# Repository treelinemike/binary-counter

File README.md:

# binary-counter
AVR binary counter for LED display - used to check synchronization of stereo camera systems

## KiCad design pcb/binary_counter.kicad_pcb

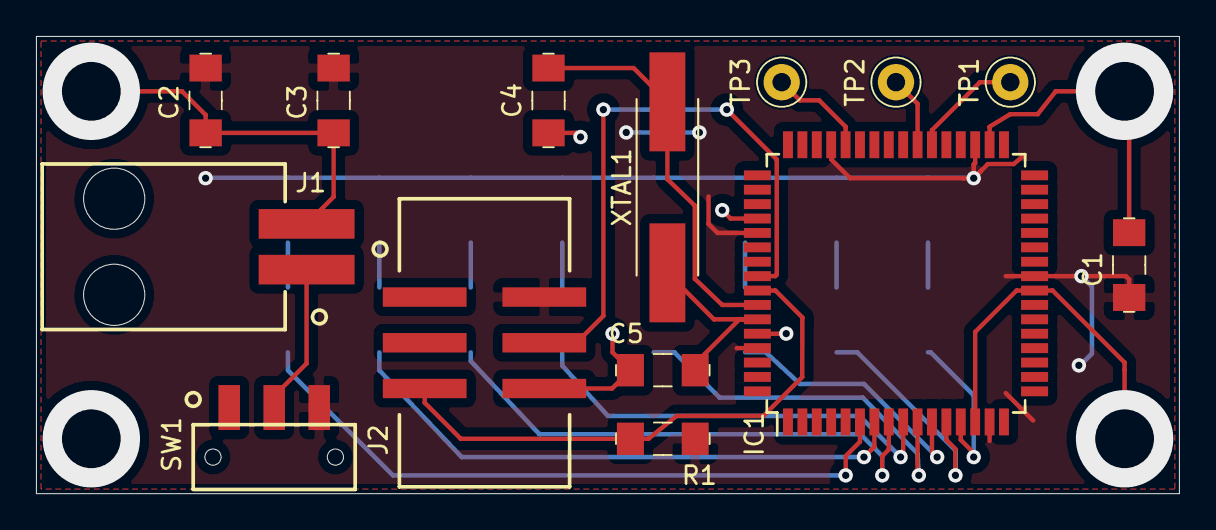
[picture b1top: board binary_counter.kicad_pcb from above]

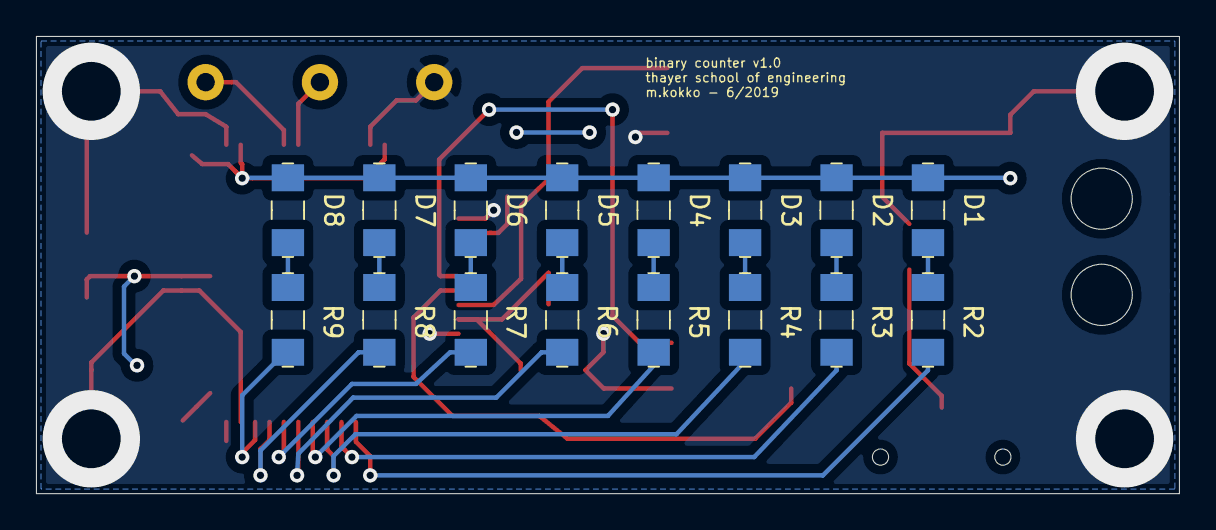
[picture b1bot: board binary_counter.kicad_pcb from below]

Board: 2 copper layers, 63.5 x 25.4 mm, 30 parts (16 on the bottom side), 25 nets.

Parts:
C1, C2: 0.1uF; 1206
C3: 10uF; 1206
C4, C5: 3pF; 1206
D1, D2, D3, D4, D5, D6, D7, D8: LTST-C150KRKT; 1206
IC1: ATXMEGA256A3BU-A; TQFP-64_14x14mm_P0.8mm
J1: Conn_01x02_Male; Molex_15_91_2025
J2: CONN_02X03; prog_header
R1: 100K; 1206
R2, R3, R4, R5, R6, R7, R8, R9: 47R0; 1206
SW1: SW_SPDT; SWITCH_CK_JS102011SAQN
TP1, TP2, TP3: 5000; Test_Point_D1.02mm
XTAL1: 16MHZ; TXC_xtal

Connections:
+3V0: C1.1, C2.1, C3.1, D1.1, D2.1, D3.1, D4.1, D5.1, D6.1, D7.1, D8.1, IC1.15, IC1.25, IC1.35, IC1.45, IC1.53, IC1.61, J2.2, R1.2, SW1.3
GND: C1.2, C2.2, C3.2, C4.1, C5.1, IC1.14, IC1.24, IC1.34, IC1.44, IC1.52, IC1.60, J1.2, J2.6, TP3.1
unnamed: C4.2, IC1.58, XTAL1.1
unnamed: C5.2, IC1.59, XTAL1.2
unnamed: D1.2, R2.1
unnamed: D2.2, R3.1
unnamed: D3.2, R4.1
unnamed: D4.2, R5.1
unnamed: D5.2, R6.1
unnamed: D6.2, R7.1
unnamed: D7.2, R8.1
unnamed: D8.2, R9.1
unnamed: IC1.6, R2.2
unnamed: IC1.7, R3.2
unnamed: IC1.8, R4.2
unnamed: IC1.9, R5.2
unnamed: IC1.10, R6.2
unnamed: IC1.11, R7.2
unnamed: IC1.12, R8.2
unnamed: IC1.13, R9.2
unnamed: IC1.38, TP1.1
unnamed: IC1.39, TP2.1
unnamed: IC1.56, J2.4
unnamed: IC1.57, J2.5, R1.1
unnamed: J1.1, SW1.2

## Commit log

2019-05-24 added eclipse project
2019-05-24 ignore build directory
2019-05-24 switched to displaying inverted count since hardware configuration sinks LEDs to MCU
2019-06-17 added kicad files, copied from orthosensor project
2019-06-17 started revising schematic and specifying components.
2019-06-18 continued adding footprints, etc.
2019-06-18 finished adding footprints and started laying out board
2019-06-18 continued PCB layout, all components in appropriate locations now
2019-06-18 changed pcb vendor to oshpark
2019-06-19 added schematic notes, changed R2-9 to 27R0 to accomodate I/O pin input impedance
2019-06-19 finished first pass at pcb layout
2019-06-19 tweaked pcb layout, passes default drc
2019-06-19 updated drcs
2019-06-19 removed mod file
2019-06-19 removed temp file
2019-06-19 added gerbers
2019-06-19 regenerated gerbers without tenting, ordered from oshpark
2019-06-19 regenerated gerbers without tenting, ordered from oshpark - included gerber zip file
2019-06-27 corrected LED port for PCB, added info on programming fuse byte 4 to disable JTAG (enabled by default), and deleted an extraneous PDF
2019-06-27 minor comment tweaks in code
2019-06-28 changed frame rate to 59.94Hz
